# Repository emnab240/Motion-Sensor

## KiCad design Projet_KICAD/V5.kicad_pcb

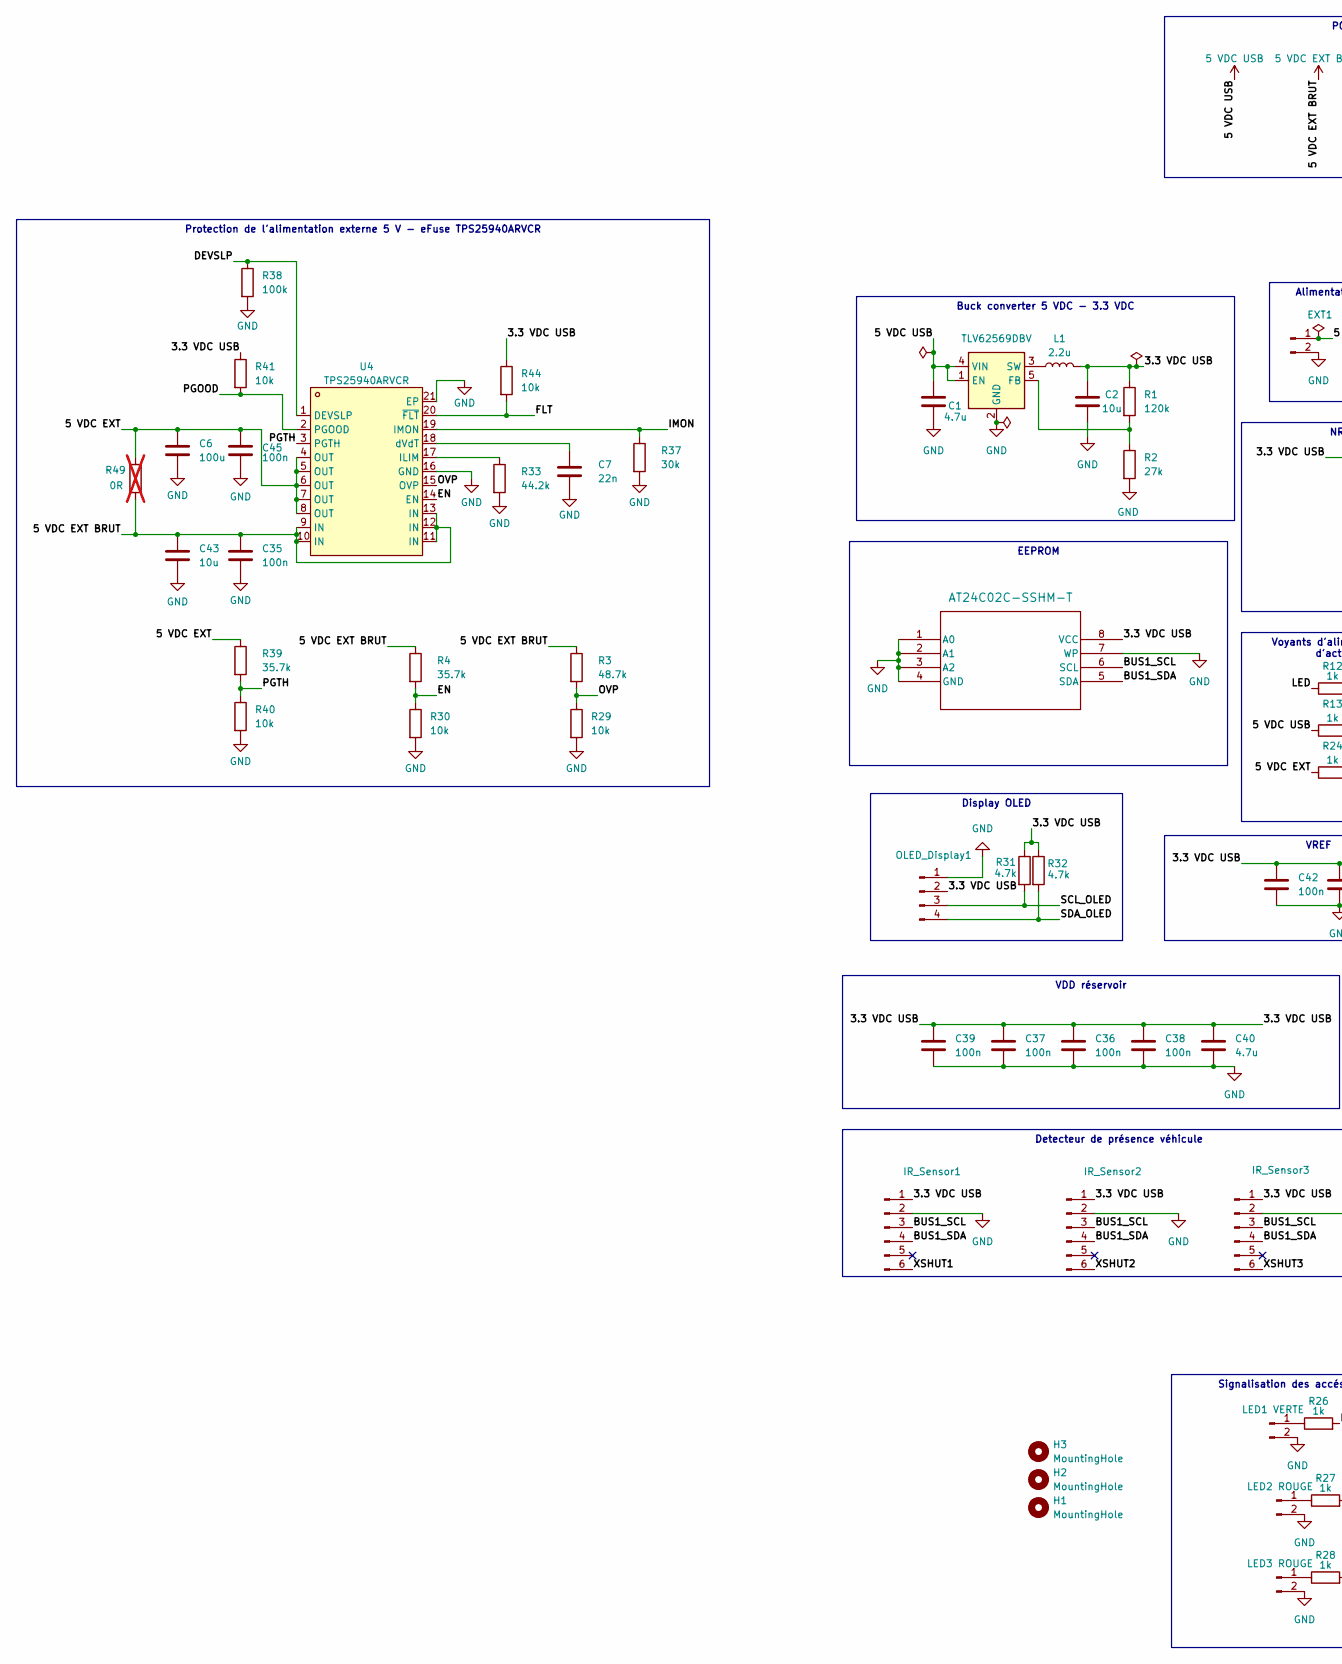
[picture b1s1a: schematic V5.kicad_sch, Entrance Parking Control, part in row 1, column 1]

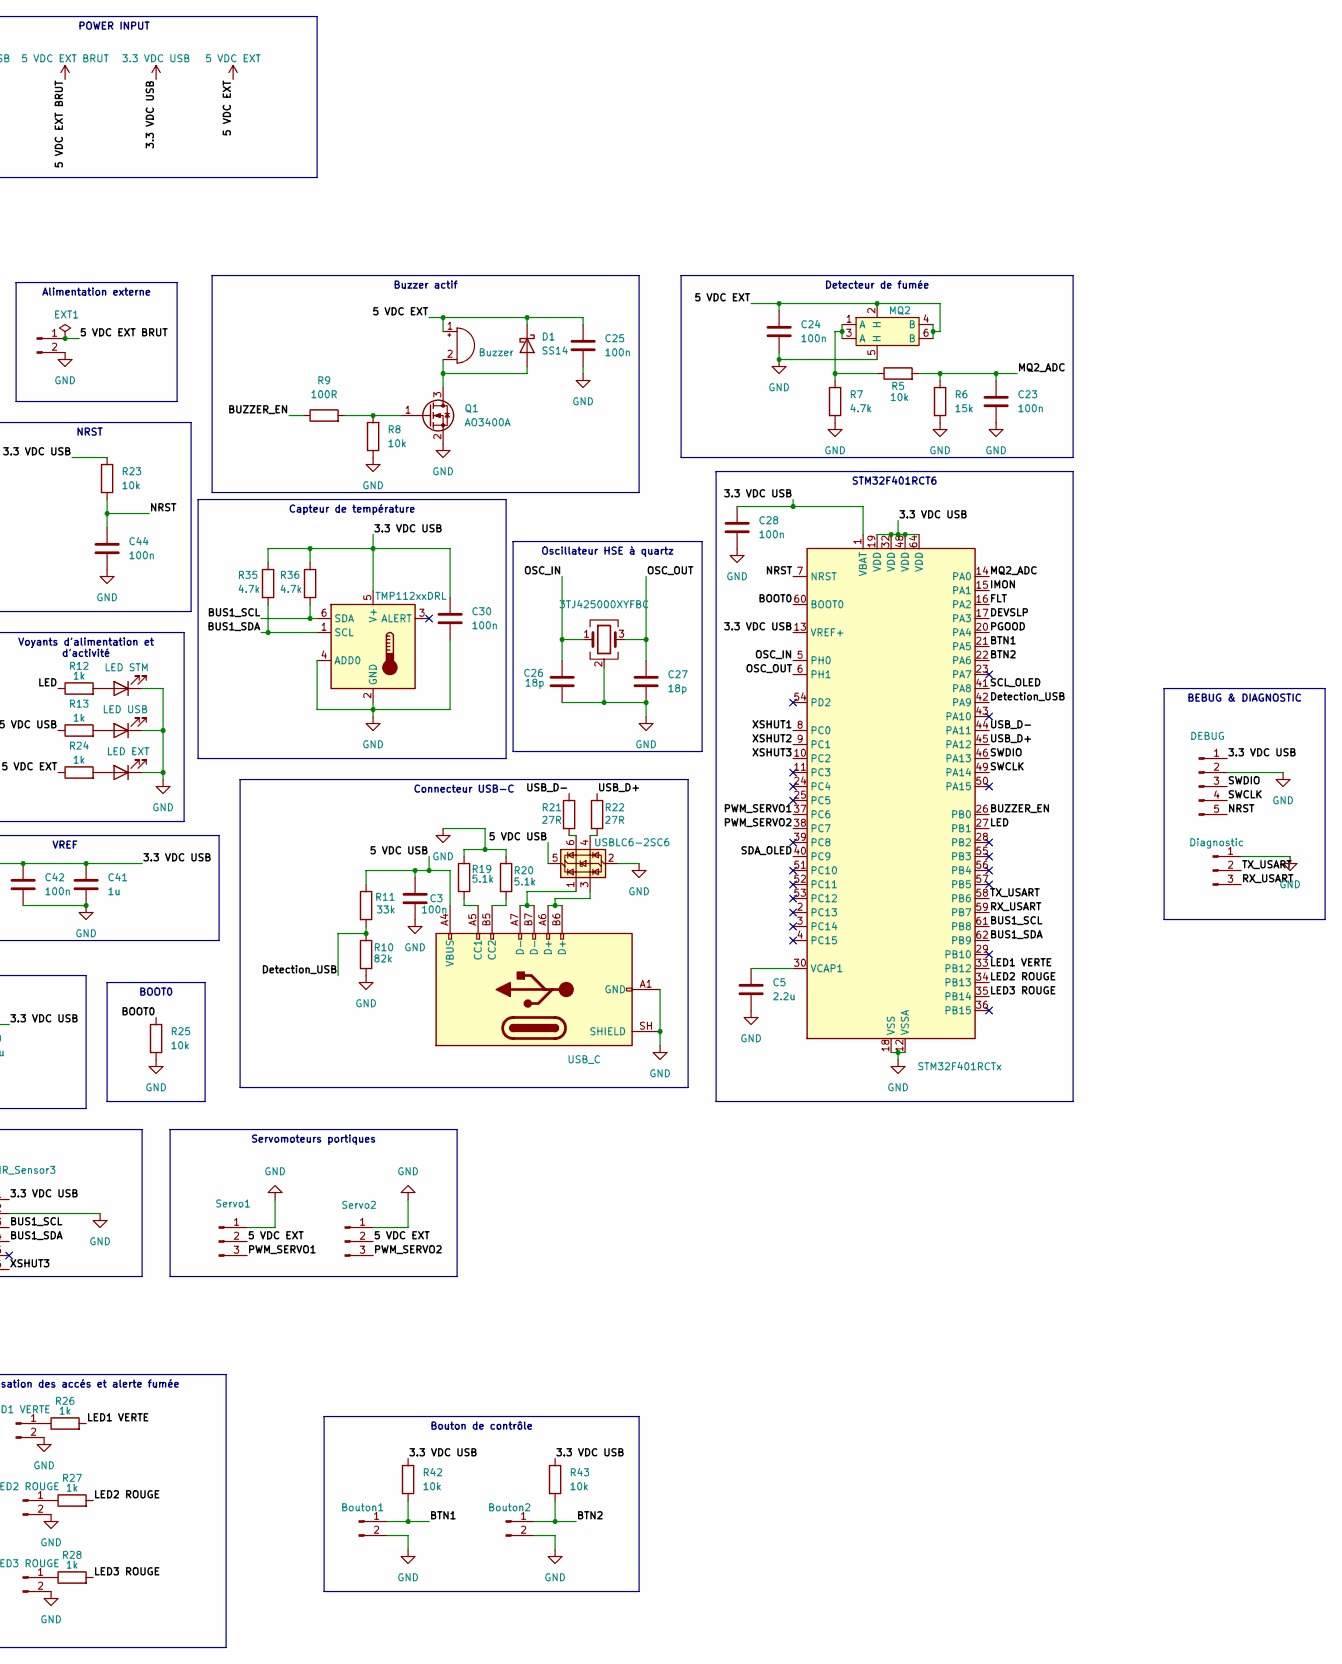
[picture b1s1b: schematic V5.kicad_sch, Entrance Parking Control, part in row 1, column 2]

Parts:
BZ1: Buzzer; Buzzer_12x9.5RM7.6; LCSC C417389
C1, C40: 4.7u; C_0603_1608Metric; LCSC C1705
C2, C43: 10u; C_0805_2012Metric; LCSC C15850
C3, C23, C24, C25, C30, C35, C36, C37, C38, C39, C42, C44, C45: 100n; C_0603_1608Metric; LCSC C108079
C5: 2.2u; C_0603_1608Metric; LCSC C1607
C6: 100u; CP_Elec_6.3x7.7; LCSC C3338
C7: 22n; C_0402_1005Metric; LCSC C1532
C26, C27: 18p; C_0603_1608Metric; LCSC C1647
C28: 100n; C_0402_1005Metric; LCSC C1525
C41: 1u; C_0603_1608Metric; LCSC C15849
D1: SS14; D_SMA
D3: LED STM; LED_0805_2012Metric; LCSC C2296
D4: LED USB; LED_0805_2012Metric; LCSC C2297
D5: LED EXT; LED_0805_2012Metric; LCSC C2297
EXT1: Conn_01x02_Pin; PinHeader_1x02_P2.54mm_Vertical; LCSC C492401
H1, H2, H3: MountingHole; MountingHole_3.2mm_M3
IR_Sensor1, IR_Sensor2, IR_Sensor3: Conn_01x06_Pin; PinHeader_1x06_P2.54mm_Vertical; LCSC C492405
J1: LED1 VERTE; PinHeader_1x02_P2.54mm_Vertical; LCSC C492401
J2: LED2 ROUGE; PinHeader_1x02_P2.54mm_Vertical; LCSC C492401
J3: LED3 ROUGE; PinHeader_1x02_P2.54mm_Vertical; LCSC C492401
J4: DEBUG; PinHeader_1x05_P2.54mm_Vertical; LCSC C492404
J5: Diagnostic; PinHeader_1x03_P2.54mm_Vertical; LCSC C7501581
J6: Bouton1; PinHeader_1x02_P2.54mm_Vertical; LCSC C492401
J7: Bouton2; PinHeader_1x02_P2.54mm_Vertical; LCSC C492401
J12: USB_C; USB-C_perso; LCSC C7095263
L1: 2.2u; L_Sunlord_SWPA4030S; LCSC C279948
MQ2: MQ2
OLED_Display1: Conn_01x04_Pin; PinHeader_1x04_P2.54mm_Vertical; LCSC C492403
Q1: AO3400A; SOT-23
R1: 120k; R_0805_2012Metric; LCSC C17436
R2: 27k; R_0805_2012Metric; LCSC C17593
R3: 48.7k; R_0402_1005Metric; LCSC C2684519
R4, R39: 35.7k; R_0402_1005Metric; LCSC C2681604
R5, R8, R23, R25, R42, R43: 10k; R_0603_1608Metric; LCSC C25804
R6: 15k; R_0603_1608Metric; LCSC C22809
R7, R31, R32, R35, R36: 4.7k; R_0603_1608Metric; LCSC C23162
R9: 100R; R_0603_1608Metric; LCSC C22775
R10: 82k; R_0603_1608Metric; LCSC C23254
R11: 33k; R_0603_1608Metric; LCSC C4216
R12, R13, R24, R26, R27, R28: 1k; R_0603_1608Metric; LCSC C21190
R19, R20: 5.1k; R_0603_1608Metric; LCSC C23186
R21, R22: 27R; R_0402_1005Metric; LCSC C25100
R29, R30, R40: 10k; R_0402_1005Metric; LCSC C328417
R33: 44.2k; R_0402_1005Metric; LCSC C11565
R37: 30k; R_0402_1005Metric; LCSC C25776
R38: 100k; R_0402_1005Metric; LCSC C25530
R41, R44: 10k; R_0402_1005Metric; LCSC C25531
R49: 0R; R_0805_2012Metric; LCSC C17477; not fitted
Servo1, Servo2: Conn_01x03_Pin; PinHeader_1x03_P2.54mm_Vertical; LCSC C7501581
U1: TLV62569DBV; SOT-23-5; LCSC C141836
U2: STM32F401RCTx; LQFP-64_10x10mm_P0.5mm; LCSC C74524
U3: TMP112xxDRL; SOT-563; LCSC C28927
U4: TPS25940ARVCR; WQFN-20_L4.0-W3.0-P0.50-BL-EP; MPN TPS25940ARVCR; LCSC Part C2653873
U5: USBLC6-2SC6; SOT-23-6; LCSC C7519
U7: AT24C02C-SSHM-T; SOIC-8_3.9x4.9mm_P1.27mm; LCSC C6203
Y2: 3TJ425000XYFBC; Crystal_SMD_3225-4Pin_3.2x2.5mm; LCSC C2149071

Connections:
3.3 VDC USB: C2.1, C28.2, C30.1, C36.2, C37.2, C38.2, C39.2, C40.1, C41.1, C42.2, IR_Sensor1.1, IR_Sensor2.1, IR_Sensor3.1, J4.1, L1.2, OLED_Display1.2, R1.1, R23.1, R31.1, R32.1, R35.1, R36.1, R41.1, R42.1, R43.1, R44.1, U2.1 (VBAT), U2.13 (VREF+), U2.19 (VDD), U2.32 (VDD), U2.48 (VDD), U2.64 (VDD), U3.5 (V+), U7.8 (VCC)
5 VDC EXT: BZ1.1 (+), C6.1, C24.1, C25.1, C45.1, D1.1 (K), MQ2.2 (H), MQ2.4 (B), MQ2.6 (B), R24.1, R39.1, R49.1, Servo1.2, Servo2.2, U4.4 (OUT), U4.5 (OUT), U4.6 (OUT), U4.7 (OUT), U4.8 (OUT)
5 VDC EXT BRUT: C35.1, C43.1, EXT1.1, R3.1, R4.1, R49.2, U4.9 (IN), U4.10 (IN), U4.11 (IN), U4.12 (IN), U4.13 (IN)
5 VDC USB: C1.1, C3.1, J12.A4 (VBUS), J12.A9 (VBUS), J12.B4 (VBUS), J12.B9 (VBUS), R11.1, R13.1, U1.1 (EN), U1.4 (VIN), U5.5 (VBUS)
/BOOT0: R25.1, U2.60 (BOOT0)
/BTN1: J6.1, R42.2, U2.21 (PA5)
/BTN2: J7.1, R43.2, U2.22 (PA6)
/BUS1_SCL: IR_Sensor1.3, IR_Sensor2.3, IR_Sensor3.3, R36.2, U2.61 (PB8), U3.6 (SDA), U7.6 (SCL)
/BUS1_SDA: IR_Sensor1.4, IR_Sensor2.4, IR_Sensor3.4, R35.2, U2.62 (PB9), U3.1 (SCL), U7.5 (SDA)
/BUZZER_EN: R9.1, U2.26 (PB0)
/DEVSLP: R38.1, U2.17 (PA3), U4.1 (DEVSLP)
/Detection_USB: R10.1, R11.2, U2.42 (PA9)
/EN: R4.2, R30.1, U4.14 (EN)
/FLT: R44.2, U2.16 (PA2), U4.20 (~FLT)
/IMON: R37.1, U2.15 (PA1), U4.19 (IMON)
/LED: R12.1, U2.27 (PB1)
/LED1 VERTE: R26.2, U2.33 (PB12)
/LED2 ROUGE: R27.2, U2.34 (PB13)
/LED3 ROUGE: R28.2, U2.35 (PB14)
/MQ2_ADC: C23.1, R5.2, R6.1, U2.14 (PA0)
/NRST: C44.2, J4.5, R23.2, U2.7 (NRST)
/OSC_IN: C26.1, U2.5 (PH0), Y2.1
/OSC_OUT: C27.1, U2.6 (PH1), Y2.3
/OVP: R3.2, R29.1, U4.15 (OVP)
/PGOOD: R41.2, U2.20 (PA4), U4.2 (PGOOD)
/PGTH: R39.2, R40.1, U4.3 (PGTH)
/PWM_SERVO1: Servo1.3, U2.37 (PC6)
/PWM_SERVO2: Servo2.3, U2.38 (PC7)
/RX_USART: J5.3, U2.59 (PB7)
/SCL_OLED: OLED_Display1.3, R31.2, U2.41 (PA8)
/SDA_OLED: OLED_Display1.4, R32.2, U2.40 (PC9)
/SWCLK: J4.4, U2.49 (PA14)
/SWDIO: J4.3, U2.46 (PA13)
/TX_USART: J5.2, U2.58 (PB6)
/USB_D+: R22.1, U2.45 (PA12)
/USB_D-: R21.1, U2.44 (PA11)
/XSHUT1: IR_Sensor1.6, U2.8 (PC0)
/XSHUT2: IR_Sensor2.6, U2.9 (PC1)
/XSHUT3: IR_Sensor3.6, U2.10 (PC2)
GND: C1.2, C2.2, C3.2, C5.2, C6.2, C7.2, C23.2, C24.2, C25.2, C26.2, C27.2, C28.1, C30.2, C35.2, C36.1, C37.1, C38.1, C39.1, C40.2, C41.2, C42.1, C43.2, C44.1, C45.2, D3.1 (K), D4.1 (K), D5.1 (K), EXT1.2, IR_Sensor1.2, IR_Sensor2.2, IR_Sensor3.2, J1.2, J2.2, J3.2, J4.2, J5.1, J6.2, J7.2, J12.A1 (GND), J12.A12 (GND), J12.B1 (GND), J12.B12 (GND), J12.SH (SHIELD), MQ2.5 (H), OLED_Display1.1, Q1.2 (S), R2.2, R6.2, R7.2, R8.1, R10.2, R19.1, R20.1, R25.2, R29.2, R30.2, R33.2, R37.2, R38.2, R40.2, Servo1.1, Servo2.1, U1.2 (GND), U2.12 (VSSA), U2.18 (VSS), U2.31 (VSS), U2.47 (VSS), U2.63 (VSS), U3.2 (GND), U3.4 (ADD0), U4.16 (GND), U4.21 (EP), U5.2 (GND), U7.1 (A0), U7.2 (A1), U7.3 (A2), U7.4 (GND), U7.7 (WP), Y2.2 (G), Y2.4 (G)
unnamed: BZ1.2 (-), D1.2 (A), Q1.3 (D)
unnamed: D3.2 (A), R12.2
unnamed: D4.2 (A), R13.2
unnamed: D5.2 (A), R24.2
unnamed: J1.1, R26.1
unnamed: J2.1, R27.1
unnamed: J3.1, R28.1
unnamed: J12.A5 (CC1), R19.2
unnamed: J12.B5 (CC2), R20.2
unnamed: J12.A6 (D+), J12.B6 (D+), U5.3 (I/O2)
unnamed: J12.A7 (D-), J12.B7 (D-), U5.1 (I/O1)
unnamed: MQ2.1 (A), MQ2.3 (A), R5.1, R7.1
unnamed: Q1.1 (G), R8.2, R9.2
unnamed: R21.2, U5.6 (I/O1)
unnamed: R22.2, U5.4 (I/O2)
unnamed: R1.2, R2.1, U1.5 (FB)
unnamed: L1.1, U1.3 (SW)
unnamed: C5.1, U2.30 (VCAP1)
unnamed: R33.1, U4.17 (ILIM)
unnamed: C7.1, U4.18 (dVdT)

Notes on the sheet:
Capteur de température
Buzzer actif
Buck converter 5 VDC - 3.3 VDC
Detecteur de fumée
BEBUG & DIAGNOSTIC
Protection de l'alimentation externe 5 V - eFuse TPS25940ARVCR
Bouton de contrôle
VREF
STM32F401RCT6
BOOT0
Connecteur USB-C
EEPROM
Detecteur de présence véhicule
POWER INPUT
Signalisation des accés et alerte fumée
Display OLED
Servomoteurs portiques
VDD réservoir
NRST
Voyants d'alimentation et d'activité
Alimentation externe
Oscillateur HSE à quartz

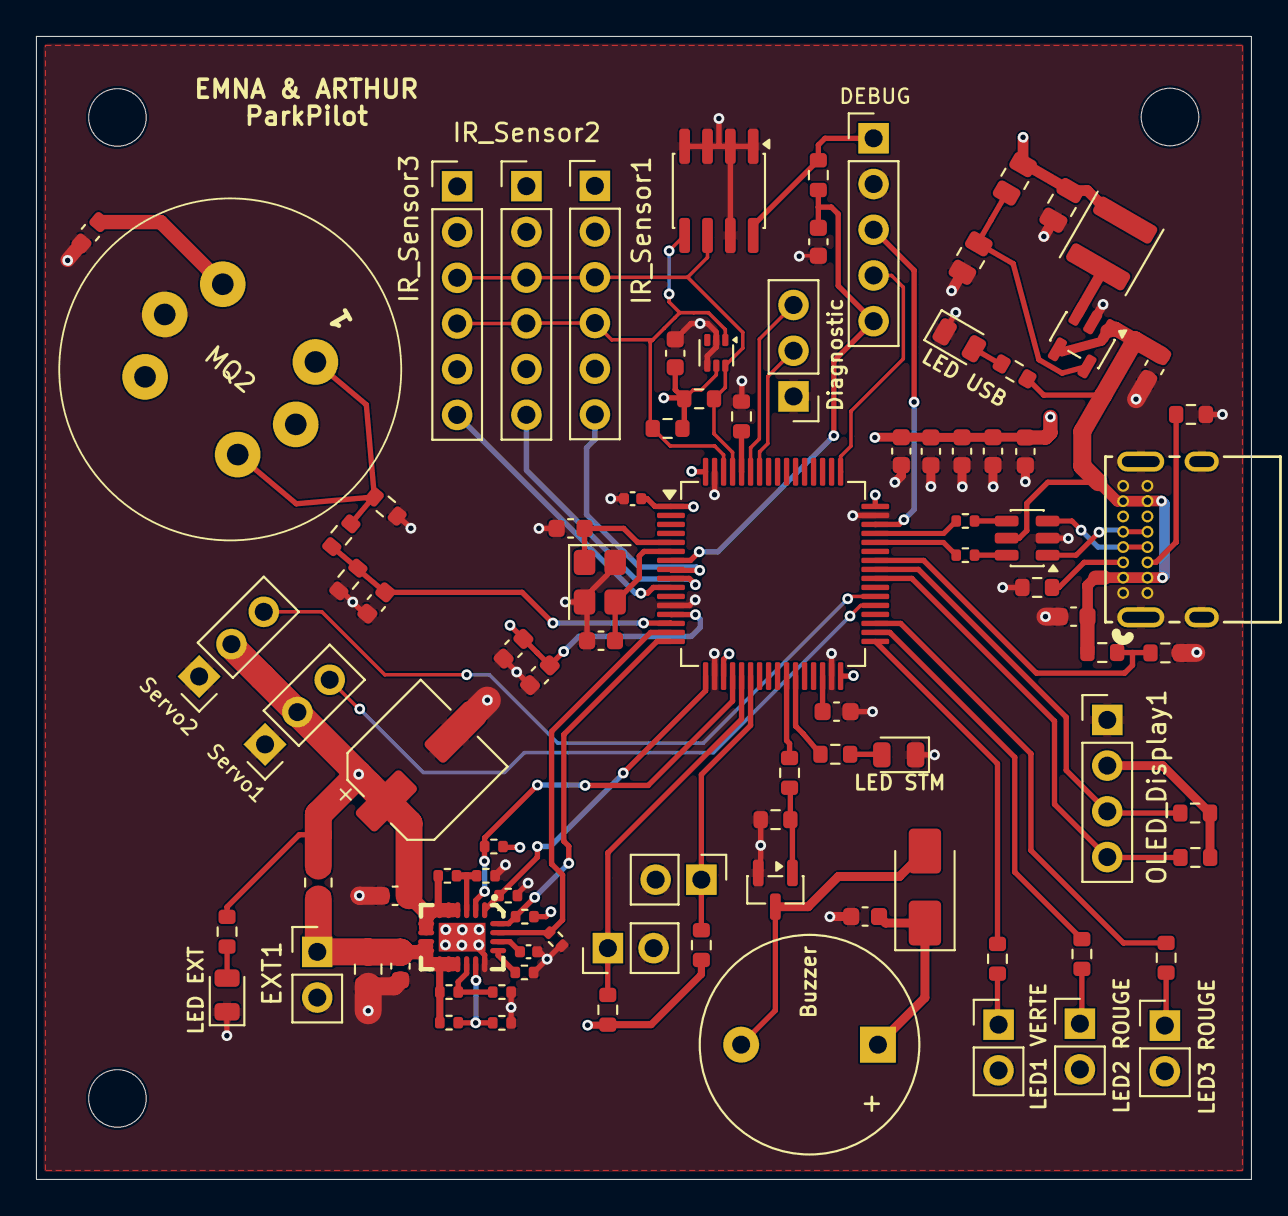
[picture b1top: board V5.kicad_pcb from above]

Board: 4 copper layers, 67.5 x 63.5 mm, 96 parts (0 on the bottom side), 60 nets.

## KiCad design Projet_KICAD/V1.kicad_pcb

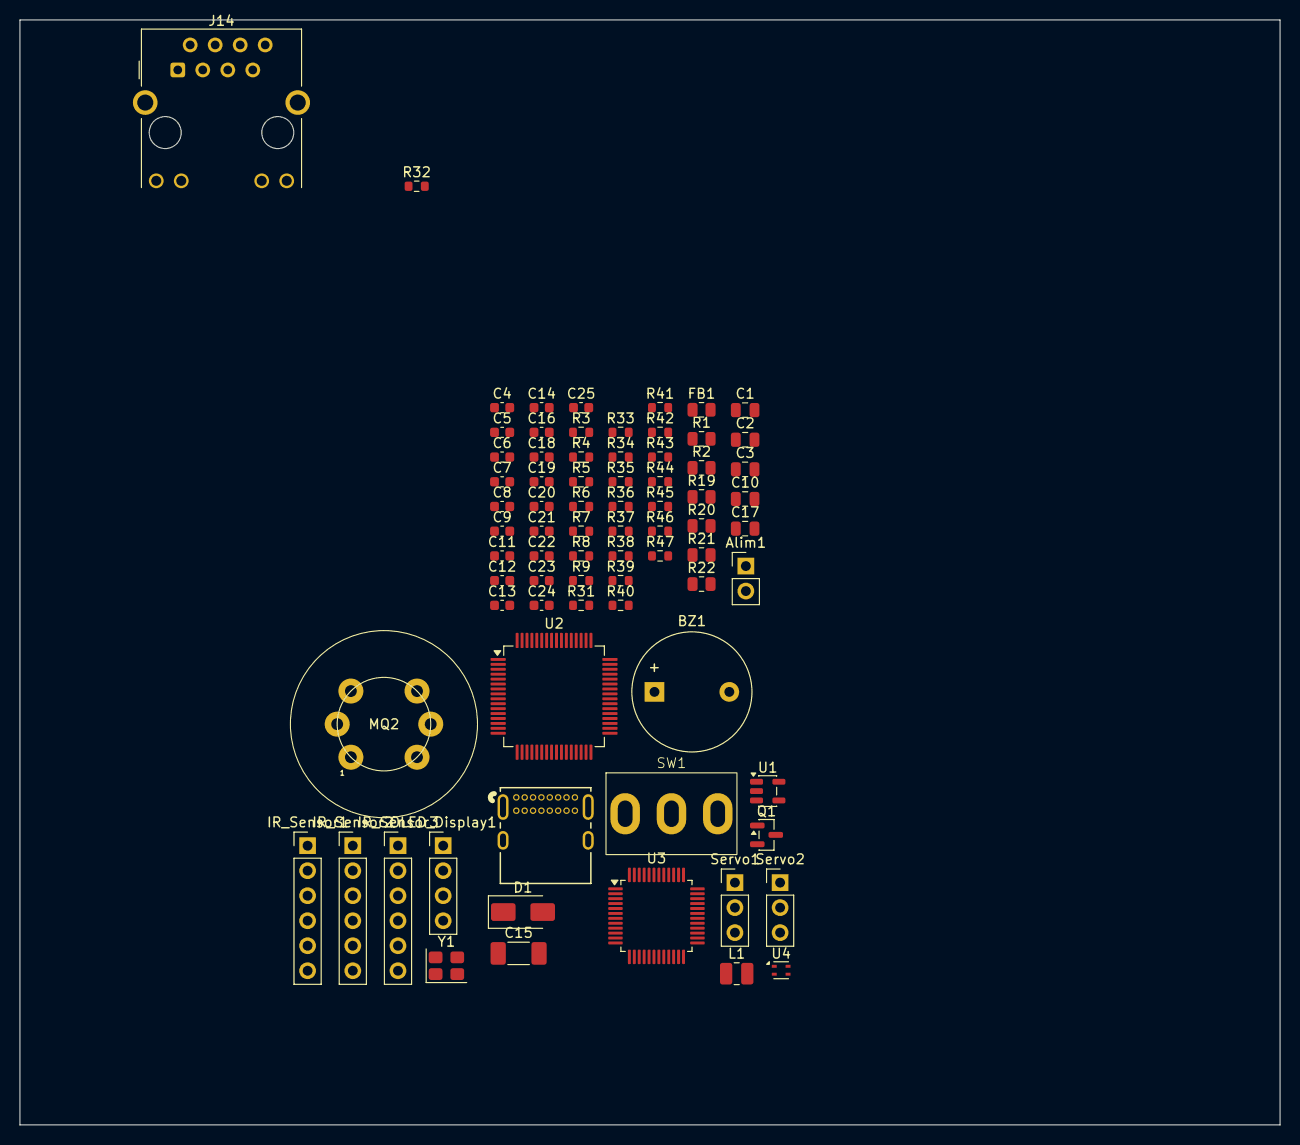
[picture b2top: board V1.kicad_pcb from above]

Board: 4 copper layers, 128.0 x 112.2 mm, 76 parts (0 on the bottom side), 55 nets, no tracks yet.

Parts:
Alim1: Conn_01x02_Pin; PinHeader_1x02_P2.54mm_Vertical
BZ1: Buzzer; Buzzer_12x9.5RM7.6
C1, C17: 4.7u; C_0805_2012Metric
C2, C10: 10u; C_0805_2012Metric
C3: 100n; C_0805_2012Metric
C4, C5, C6, C7, C8, C9, C21, C22, C23, C24, C25: 100n; C_0603_1608Metric
C11: 22n; C_0603_1608Metric
C12, C13: 6.8nF; C_0603_1608Metric
C14, C16: 10n; C_0603_1608Metric
C15: 1n/2k; C_1808_4520Metric
C18: 27p; C_0603_1608Metric
C19: 27pF; C_0603_1608Metric
C20: 10u; C_0603_1608Metric
D1: SS14; D_SMA
FB1: CBG201209U121T; R_0805_2012Metric
IR_Sensor1, IR_Sensor2, IR_Sensor3: Conn_01x06_Pin; PinHeader_1x06_P2.54mm_Vertical
J12: USB_C_Receptacle_USB2.0_14P; CONN16_USB4085-GF-A_GCT
J14: RJ45_Hanrun_HR911105A_Horizontal
L1: 2.2u; L_1008_2520Metric
MQ2: MQ2
OLED_Display1: Conn_01x04_Pin; PinHeader_1x04_P2.54mm_Vertical
Q1: AO3400A; SOT-23
R1: 120k; R_0805_2012Metric
R2: 27k; R_0805_2012Metric
R3, R4, R5, R8, R45, R46, R47: 10k; R_0603_1608Metric
R6: 15k; R_0603_1608Metric
R7: 4.7k; R_0603_1608Metric
R9: 100R; R_0603_1608Metric
R19, R20: 5.1k; R_0805_2012Metric
R21, R22: 27R; R_0805_2012Metric
R31, R32, R33, R34, R44: 0R; R_0603_1608Metric
R35, R36, R38, R39: 49R9; R_0603_1608Metric
R37: 10R; R_0603_1608Metric
R40: 12.4k; R_0603_1608Metric
R41, R42: 330R; R_0603_1608Metric
R43: 1M; R_0603_1608Metric
SW1: SW_SPDT; Interrupteur_MT-0-102-A101-M200-RS
Servo1, Servo2: Conn_01x03_Pin; PinHeader_1x03_P2.54mm_Vertical
U1: TLV62569DBV; SOT-23-5
U2: STM32F401RCTx; LQFP-64_10x10mm_P0.5mm
U3: W5500; LQFP-48_7x7mm_P0.5mm
U4: SHT4x; Sensirion_DFN-4_1.5x1.5mm_P0.8mm_SHT4x_NoCentralPad
Y1: Crystal_GND24; Crystal_SMD_3225-4Pin_3.2x2.5mm

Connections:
/3.3 AVDC: C4.1, C5.1, C6.1, C7.1, C8.1, C9.1, C10.1, FB1.2, R35.1, R36.1, R37.1, U3.4 (AVDD), U3.8 (AVDD), U3.11 (AVDD), U3.15 (AVDD), U3.17 (AVDD), U3.21 (AVDD)
/3.3 VDC: C2.1, C20.1, C21.1, C22.1, FB1.1, IR_Sensor1.1, IR_Sensor2.1, IR_Sensor3.1, J14.9, J14.12, L1.2, OLED_Display1.2, R1.1, R3.1, R4.1, R45.2, R46.2, R47.2, U3.28 (VDD), U4.3 (VDD)
/5 VDC: BZ1.1 (+), C1.1, C24.1, C25.1, D1.1 (K), MQ2.2 (H), MQ2.4 (B), MQ2.6 (B), SW1.2 (B), Servo1.2, Servo2.2, U1.1 (EN), U1.4 (VIN)
/5 VDC ALIM: Alim1.1, SW1.3 (C)
/5 VDC USB: C3.1, J12.A4 (VBUS), J12.A9 (VBUS), J12.B4 (VBUS), J12.B9 (VBUS), SW1.1 (A)
/ACTLED: R41.2, U3.27 (ACTLED)
/BUS1_SCL: IR_Sensor1.3, IR_Sensor2.3, IR_Sensor3.3, R4.2, U2.61 (PB8), U4.2 (SCL)
/BUS1_SDA: IR_Sensor1.4, IR_Sensor2.4, IR_Sensor3.4, R3.2, U2.62 (PB9), U4.1 (SDA)
/BUZZER_EN: R9.1, U2.26 (PB0)
/LINKLED: R42.2, U3.25 (LINKLED)
/MQ2_ADC: C23.1, R5.2, R6.1, U2.14 (PA0)
/PWM_SERVO1: Servo1.3, U2.37 (PC6)
/PWM_SERVO2: Servo2.3, U2.38 (PC7)
/SCL_OLED: OLED_Display1.3, U2.41 (PA8)
/SDA_OLED: OLED_Display1.4, U2.40 (PC9)
/USB_D+: R22.1, U2.45 (PA12)
/USB_D-: R21.1, U2.44 (PA11)
/XSHUT1: IR_Sensor2.6, U2.8 (PC0)
/XSHUT2: IR_Sensor1.6, U2.9 (PC1)
/XSHUT3: IR_Sensor3.6, U2.10 (PC2)
CGND: C15.2, J14.8, J14.SH
GND: Alim1.2, C1.2, C2.2, C3.2, C4.2, C5.2, C6.2, C7.2, C8.2, C9.2, C10.2, C11.2, C14.2, C15.1, C16.2, C17.2, C18.2, C19.2, C20.2, C21.2, C22.2, C23.2, C24.2, C25.2, IR_Sensor1.2, IR_Sensor2.2, IR_Sensor3.2, J12.A1 (GND), J12.A12 (GND), J12.B1 (GND), J12.B12 (GND), J12.SH (SHIELD), MQ2.5 (H), OLED_Display1.1, Q1.2 (S), R2.2, R6.2, R7.2, R8.1, R19.1, R20.1, R40.2, Servo1.1, Servo2.1, U1.2 (GND), U3.3 (AGND), U3.9 (AGND), U3.14 (AGND), U3.16 (AGND), U3.19 (AGND), U3.29 (GND), U3.48 (AGND), U4.4 (VSS), Y1.2 (G), Y1.4 (G)
unnamed: BZ1.2 (-), D1.2 (A), Q1.3 (D)
unnamed: C12.1, R34.2, R38.1
unnamed: C13.1, R33.2, R39.1
unnamed: C19.1, R44.2, Y1.3
unnamed: J12.A5 (CC1), R19.2
unnamed: J12.B5 (CC2), R20.2
unnamed: J12.A6 (D+), J12.B6 (D+), R22.2
unnamed: J12.A7 (D-), J12.B7 (D-), R21.2
unnamed: J14.10, R41.1
unnamed: J14.11, R42.1
unnamed: C14.1, J14.5 (RCT), R38.2, R39.2
unnamed: C12.2, J14.3 (RD+)
unnamed: C13.2, J14.6 (RD-)
unnamed: C11.1, J14.4 (TCT), R37.2
unnamed: J14.1 (TD+), R32.2, R36.2
unnamed: J14.2 (TD-), R31.2, R35.2
unnamed: MQ2.1 (A), MQ2.3 (A), R5.1, R7.1
unnamed: Q1.1 (G), R8.2, R9.2
unnamed: R1.2, R2.1, U1.5 (FB)
unnamed: L1.1, U1.3 (SW)
unnamed: U2.18 (VSS), U2.31 (VSS), U2.47 (VSS), U2.63 (VSS)
unnamed: C16.1, U3.22 (1V2O)
unnamed: R40.1, U3.10 (EXRES1)
unnamed: R45.1, U3.45 (PMODE0)
unnamed: R46.1, U3.44 (PMODE1)
unnamed: R47.1, U3.43 (PMODE2)
unnamed: R33.1, U3.5 (RXN)
unnamed: R34.1, U3.6 (RXP)
unnamed: C17.1, U3.20 (TOCAP)
unnamed: R31.1, U3.1 (TXN)
unnamed: R32.1, U3.2 (TXP)
unnamed: C18.1, R43.1, U3.30 (XI/CLKIN), Y1.1
unnamed: R43.2, R44.1, U3.31 (XO)

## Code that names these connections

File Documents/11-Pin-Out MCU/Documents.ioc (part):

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Mcu.Name=STM32F401R(B-C)Tx
Mcu.Package=LQFP64
Mcu.UserName=STM32F401RCTx
PA0-WKUP.GPIOParameters=GPIO_Label,GPIO_Mode
PA0-WKUP.GPIO_Label=MQ2_ADC
PA0-WKUP.GPIO_Mode=GPIO_MODE_ANALOG
PA0-WKUP.Signal=ADCx_IN0
PA1.GPIOParameters=GPIO_Label
PA1.GPIO_Label=IMON
PA1.Signal=ADCx_IN1
PA11.Mode=Device_Only
PA11.Signal=USB_OTG_FS_DM
PA12.Mode=Device_Only
PA12.Signal=USB_OTG_FS_DP
PA13.Mode=Serial_Wire
PA13.Signal=SYS_JTMS-SWDIO
PA14.Mode=Serial_Wire
PA14.Signal=SYS_JTCK-SWCLK
PA2.GPIOParameters=GPIO_Label
PA2.GPIO_Label=FLT
PA2.Signal=GPIO_Input
PA3.GPIOParameters=GPIO_Label
PA3.GPIO_Label=DEVSLEEP
PA3.Signal=GPIO_Output
PA4.GPIOParameters=GPIO_Label
PA4.GPIO_Label=PGOOD
PA4.Signal=GPIO_Input
PA5.GPIOParameters=GPIO_Label
PA5.GPIO_Label=BTN1
PA5.Signal=GPIO_Input
PA6.GPIOParameters=GPIO_Label
PA6.GPIO_Label=BTN2
PA6.Signal=GPIO_Input
PA8.GPIOParameters=GPIO_Label
PA8.GPIO_Label=I2C3_SCL_OLED
PA8.Mode=I2C
PA8.Signal=I2C3_SCL
PA9.GPIOParameters=GPIO_Label
PA9.GPIO_Label=DETECTION_USB
PA9.Signal=GPIO_Input
PB0.GPIOParameters=GPIO_Label
PB0.GPIO_Label=BUZZER_EN
PB0.Signal=GPIO_Output
PB1.GPIOParameters=GPIO_Label
PB1.GPIO_Label=LED_STM
PB1.Signal=GPIO_Output
PB12.GPIOParameters=GPIO_Label
PB12.GPIO_Label=LED1_VERTE
PB12.Signal=GPIO_Output
PB13.GPIOParameters=GPIO_Label
PB13.GPIO_Label=LED2_ROUGE
PB13.Signal=GPIO_Output
PB14.GPIOParameters=GPIO_Label
PB14.GPIO_Label=LED3_ROUGE
PB14.Signal=GPIO_Output
PB6.Mode=Asynchronous
PB6.Signal=USART1_TX
PB7.Mode=Asynchronous
PB7.Signal=USART1_RX
PB8.GPIOParameters=GPIO_Label
PB8.GPIO_Label=I2C1_SCL
PB8.Mode=I2C
PB8.Signal=I2C1_SCL
PB9.GPIOParameters=GPIO_Label
PB9.GPIO_Label=I2C1_SDA
PB9.Mode=I2C
PB9.Signal=I2C1_SDA
PC0.GPIOParameters=GPIO_Label
PC0.GPIO_Label=XSHUT_IR_1
PC0.Signal=GPIO_Output
PC1.GPIOParameters=GPIO_Label
PC1.GPIO_Label=XSHUT_IR_2
PC1.Signal=GPIO_Output
PC2.GPIOParameters=GPIO_Label
PC2.GPIO_Label=XSHUT_IR_3
PC2.Signal=GPIO_Output
PC6.GPIOParameters=GPIO_Label
PC6.GPIO_Label=TIM3_CH1_SERVO1
PC6.Signal=S_TIM3_CH1
PC7.GPIOParameters=GPIO_Label
PC7.GPIO_Label=TIM3_CH2_SERVO2
PC7.Signal=S_TIM3_CH2
PC9.GPIOParameters=GPIO_Label
PC9.GPIO_Label=I2C3_SDA_OLED
PC9.Mode=I2C
PC9.Signal=I2C3_SDA
PH0\ -\ OSC_IN.Mode=HSE-External-Oscillator
PH0\ -\ OSC_IN.Signal=RCC_OSC_IN
PH1\ -\ OSC_OUT.Mode=HSE-External-Oscillator
PH1\ -\ OSC_OUT.Signal=RCC_OSC_OUT
RCC.HSE_VALUE=25000000
RCC.SYSCLKFreq_VALUE=84000000
RCC.SYSCLKSource=RCC_SYSCLKSOURCE_PLLCLK
board=custom
